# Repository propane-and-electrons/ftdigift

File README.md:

ftdigift
--------

This is a clone of the SparkFun FTDI Basic board, but in a wearable necklace form. Because people keep losing my FTDI cables at Burning Man.

### Feature Summary

* Works just like a FTDI Basic board
* Built in USB connector
* 5V or 3V3 selectable
* Technically doesn't violate Burning Man intellectual property rules regarding the man logo
* Doesn't fit that great in USB ports but does totally work
* Awkwardly small so you have to hold your Arduino or whatever at a weird angle
* Pretty red color
* You can wear it as a necklace

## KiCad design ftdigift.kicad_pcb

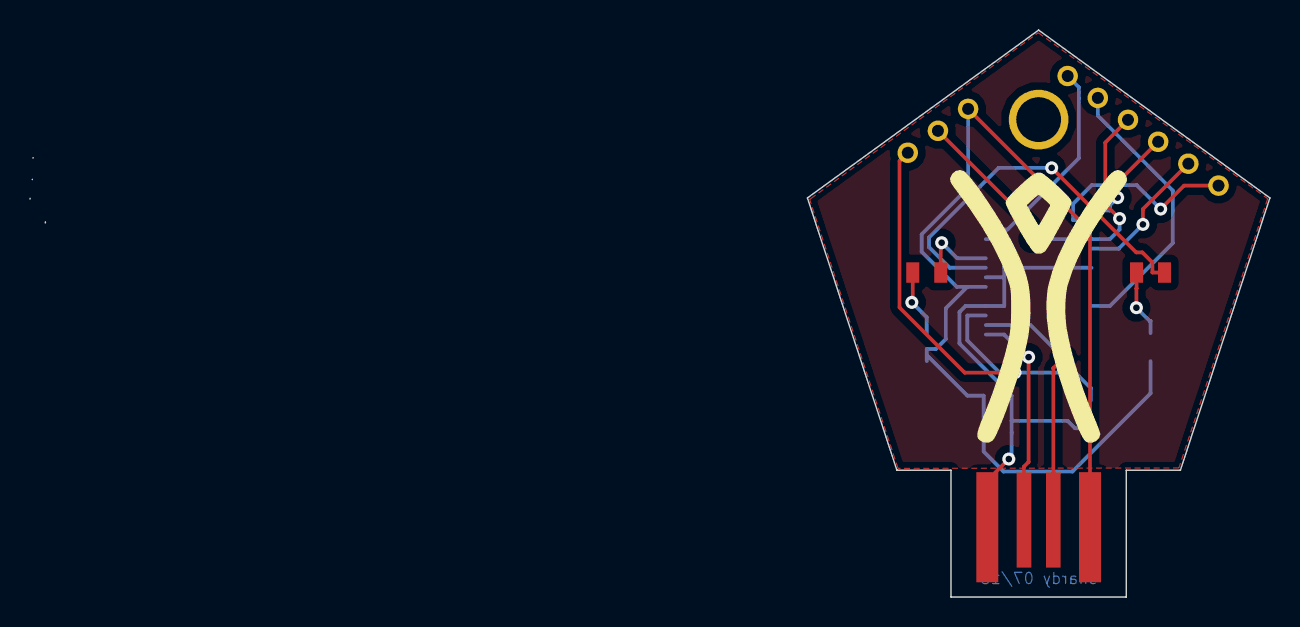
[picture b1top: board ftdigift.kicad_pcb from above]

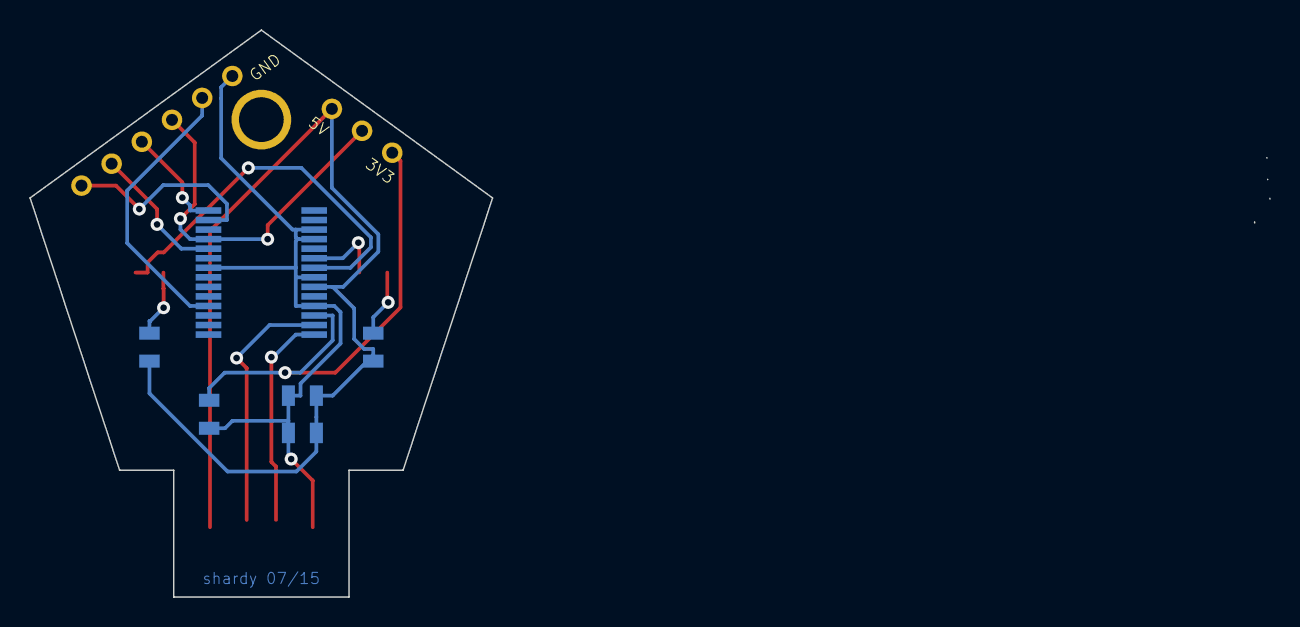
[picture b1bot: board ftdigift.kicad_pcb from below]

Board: 2 copper layers, 84.4 x 38.6 mm, 12 parts (6 on the bottom side), 14 nets.

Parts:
C1, C3: 0.1uF; SM0805
C2: 10uF; SM0805
D1: TXLED; SM0805
D2: RXLED; SM0805
H1: SCREWHOLE; 1pin
J1: USB; USB-A-PCB
P1: PWRSEL; SIL-3
P2: FTDI; SIL-6
R1, R2: 1k; SM0805
U1: FT232RLSSOP; SSOP-28_5.3x10.2mm_Pitch0.65mm

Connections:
+3.3V: C3.1, P1.1, U1.17
+5V: C1.1, C2.1, J1.1, P1.3, R1.1, R2.1, U1.20
/CTS: P2.2, U1.11
/DTR: P2.6, U1.2
/POWER: P1.2, P2.3, U1.4
/RXI: P2.5, U1.5
/TXO: P2.4, U1.1
GND: C1.2, C2.2, C3.2, J1.4, P2.1, U1.7, U1.18, U1.21, U1.25, U1.26
unnamed: D1.1, R1.2
unnamed: D1.2, U1.23
unnamed: D2.1, R2.2
unnamed: D2.2, U1.22
unnamed: J1.2, U1.16
unnamed: J1.3, U1.15

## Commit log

2015-08-18 it works
2015-08-18 moving things around
2015-08-18 adding docs
